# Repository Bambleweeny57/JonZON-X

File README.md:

# 🎵 JonZON-X AY-3-8910 Sound Expansion for ZX81

JonZON-X is a modern recreation of the ZON-X-81 Sound Box by Bi-Pak, designed for the ZX81. It uses the AY-3-8910 Programmable Sound Generator (PSG) and supports stereo line-out, optional multi-PSG expansion, and historically accurate address decoding.

This project prioritizes:
- ✅ Robust signal integrity
- ✅ Accurate control logic
- ✅ Modular expansion
- ✅ Historical preservation

---

## 🎯 Goals

- Recreate the original ZON-X-81 using AY-3-8910 (not AY-3-8912)
- Provide stereo line-out instead of onboard speaker
- Divide CPU clock as in the original design
- Support optional second and third PSGs via A5 and A6
- Document logic blocks and truth tables that match the actual schematic

---

## 🧠 Control Signal Logic

JonZON-X uses modern 74HC-series gates to derive control signals for the AY-3-8910. The address decoding is based on:

- **A0–A4**: Select the first PSG
- **A5**: Optional second PSG (replaces A4)
- **A6**: Optional third PSG (replaces A4)
- **A7**: Used in BC1 logic
- **/IOREQ**, **/WR**, **/RD**: Control timing

### Signal Derivation

| Signal | Logic Expression | Gates Used |
|--------|------------------|------------|
| **BDIR** | Derived from /IOREQ and /WR  
→ Routed through 74HC02 (inversion), 74HC08 (AND), and 74HC11 (3-input AND) | 74HC02, 74HC08, 74HC11 |
| **BC1** | Derived from /IOREQ, /WR, A2, A7, /RD  
→ Routed through 74HC02, 74HC08, and 74HC11 | 74HC02, 74HC08, 74HC11 |

There is **no AYSEL signal**—address selection is handled directly via A0–A4 (or A5/A6 for additional PSGs).

---

## 📊 Truth Table

| A0–A4 | A5/A6 | A2 | A7 | /IOREQ | /WR | /RD | BDIR | BC1 | Operation |
|------|-------|----|----|--------|-----|-----|------|-----|-----------|
| PSG 1 selected | —     | 1  | 1  | 0      | 0   | 1   | 1    | 1   | Write to register |
| PSG 1 selected | —     | 1  | 1  | 0      | 0   | 0   | 1    | 0   | Write to PSG |
| PSG 1 selected | —     | 1  | 1  | 0      | 1   | 0   | 0    | 1   | Read from PSG |
| PSG 2 selected | A5=1  | 1  | 1  | 0      | —   | —   | —    | —   | Optional second PSG |
| PSG 3 selected | A6=1  | 1  | 1  | 0      | —   | —   | —    | —   | Optional third PSG |
| Not selected   | —     | —  | —  | —      | —   | —   | 0    | 0   | Inactive |

---

## 🖼️ Visual Decode Logic

This schematic snippet shows how BDIR and BC1 are generated using 74HC02, 74HC08, and 74HC11 gates. Address selection is handled via A0–A4 (or A5/A6 for additional PSGs).

---

## 🎚️ DIP Switch Mapping for PSG Selection

JonZON-X supports up to three AY-3-8910 PSGs using configurable address lines via DIP switches. The DIP switches control A4, A5, and A6 to select which PSG is active.

| PSG   | A4 | A5 | A6 | Address (Binary) | Address (Decimal) |
|-------|----|----|----|------------------|-------------------|
| PSG1  | 1  | 0  | 0  | `11111111`       | 255               |
| PSG2  | 0  | 1  | 0  | `11101111`       | 239               |
| PSG3  | 0  | 0  | 1  | `11011111`       | 223               |

- **A4, A5, A6** are mutually exclusive: only one should be active at a time.
- These bits are part of the PSG register select address.
- DIP switches override the default A4–A6 lines from the ZX81.

This mapping allows users to select which PSG responds to register writes, enabling multi-chip expansion and stereo mixing.

---

## 📚 Historical References

- [ZON-X-81 Archive (1982 Bi-Pak)](https://archive.org/details/ZON_X-81_1982_Bi-Pak_GB)
- [RevSpace ZX81 PSG Expansion](https://revspace.nl/Zon_ZX-81_Programmable_Sound_Generator_expansion_for_ZX81PLUS35_with_working_SD-Card)
- [Mahjongg2 ZON-Compatible PSG](https://github.com/mahjongg2/ZON-compatible-PSG-with-SD-interface-for-ZX81plus35-ZX81)
- [Micromusic Article](https://www.muzines.co.uk/articles/micromusic/4456)
- [ZX8081 Clone Log](https://hackaday.io/project/184361-zx8081-homebrew-clone/log/203915-my-project-log-jan-mar2021)

---

## 🛠️ Future Plans

If the initial revision works, future additions may include:
- RAM and ROM expansion
- Joystick port
- Enhanced stereo mixing

---

### 🧪 Test 1: Test Routine

```basic
10 REM ZONTEST1
20 LET A=16514
30 POKE A,62
40 LET A=A+1
50 POKE A,0
60 LET A=A+1
70 POKE A,211
80 LET A=A+1
90 POKE A,0
100 LET A=A+1
110 POKE A,201
120 POKE 16515,7
130 POKE 16516,255
140 RAND USR 16514
150 POKE 16515,8
160 POKE 16516,191
170 RAND USR 16514
180 POKE 16515,13
190 POKE 16516,9
200 RAND USR 16514
210 GOTO 210
```
- 🔊 ZONTEST1 – Basic Tone Setup: [zontest1.p](https://github.com/jgratton72/JonZON-X/blob/master/Tests/zontest1.p)

### 🧪 Test 2: Envelope & Stereo Test

```basic
10 REM ZONTEST2
20 LET A=16514
30 POKE A,62
40 LET A=A+1
50 POKE A,0
60 LET A=A+1
70 POKE A,211
80 LET A=A+1
90 POKE A,0
100 LET A=A+1
110 POKE A,201
120 POKE 16515,7
130 POKE 16516,255
140 RAND USR 16514
150 POKE 16515,8
160 POKE 16516,191
170 RAND USR 16514
180 POKE 16515,13
190 POKE 16516,9
200 RAND USR 16514
210 LET E=0
220 POKE 16515,13
230 POKE 16516,E
240 RAND USR 16514
250 LET I=0
260 LET I=I+1
270 IF I<1000 THEN GOTO 260
280 LET E=E+1
290 IF E<16 THEN GOTO 220
300 GOTO 210
```
- 🎛️ ZONTEST2 – Envelope & Stereo: [zontest2.p](https://github.com/jgratton72/JonZON-X/blob/master/Tests/zontest2.p)

### 🧪 Test 3: Envelope Period Sweep

```basic
10 REM ZONTEST3
20 LET A=16514
30 POKE A,62
40 LET A=A+1
50 POKE A,0
60 LET A=A+1
70 POKE A,211
80 LET A=A+1
90 POKE A,0
100 LET A=A+1
110 POKE A,201
120 POKE 16515,7
130 POKE 16516,255
140 RAND USR 16514
150 POKE 16515,8
160 POKE 16516,191
170 RAND USR 16514
180 POKE 16515,13
190 POKE 16516,9
200 RAND USR 16514
210 LET P=0
220 POKE 16515,11
230 POKE 16516,P
240 RAND USR 16514
250 POKE 16515,12
260 POKE 16516,0
270 RAND USR 16514
280 LET I=0
290 LET I=I+1
300 IF I<1000 THEN GOTO 290
310 LET P=P+16
320 IF P<256 THEN GOTO 220
330 GOTO 210
```
- 📈 ZONTEST3 – Envelope Sweep: [zontest3.p](https://github.com/jgratton72/JonZON-X/blob/master/Tests/zontest3.p)

### 🧪 Test 4: DIP-Selectable PSG Verification

```basic
10 REM ZONTEST4
20 LET A=16514
30 POKE A,62
40 LET A=A+1
50 POKE A,0
60 LET A=A+1
70 POKE A,211
80 LET A=A+1
90 POKE A,0
100 LET A=A+1
110 POKE A,201
120 POKE 16515,8
130 POKE 16516,255
140 RAND USR 16514
150 LET I=0
160 LET I=I+1
170 IF I<500 THEN GOTO 160
180 POKE 16515,8
190 POKE 16516,239
200 RAND USR 16514
210 LET I=0
220 LET I=I+1
230 IF I<500 THEN GOTO 220
240 POKE 16515,8
250 POKE 16516,223
260 RAND USR 16514
270 LET I=0
280 LET I=I+1
290 IF I<500 THEN GOTO 280
300 GOTO 120
```
- 🎚️ ZONTEST4 – DIP-Selectable PSGs: [zontest4.p](https://github.com/jgratton72/JonZON-X/blob/master/Tests/zontest4.p)

---

## 📅 Revision History

### 🔧 Rev 1.0 Testing Note — Stereo Jack Adaptation
- **Socket Type:** 3-pin stereo jacks used in place of shunted 5-pin variants.
- **Pad Bridging:** Inner pads manually jumped to outer signal pads; ground positioned at center front.
- **Trade-off:** Left and Right channels will be reversed — acceptable for initial validation.
- **Rationale:** Simplifies early testing without requiring shunt headers. Prioritizes proof-of-function over stereo fidelity

### 🔄 Rev 1.1 — Audio Jack Correction
- **Issue:** Left and Right channels were misrouted via Shunts A and B.
- **Fix:** Channel A and B were reversed in the schematic to compensate for the physical swap.
- **Impact:** Stereo output now matches expected channel mapping. Updated KiCad files reflect this correction.

### 🔄 Rev 1.2 – Stereo Output Mapping Adjustment

- **Issue**: Legacy ZON-X-81 software frequently routes noise to Channel B, but JonZON-X previously mixed Channel C to both outputs (a common pattern in other PSG devices, including the ZX Spectrum 128K). This caused noise effects to be isolated to the right channel or lost in stereo playback.
- **Fix**: Remapped stereo output:
  - Channel A → Left
  - Channel B → Mixed (Left + Right)
  - Channel C → Right  
  This ensures Channel B (the legacy noise channel) is centered in stereo output.
- **Impact**: Improved compatibility with original ZON-X-81 programs and demos. Noise effects now play as intended across both channels, preserving the sonic balance of legacy software.

### 🔄 Rev 1.3 – Logic Footprint Correction
- **Issue**: 74HTC Logic IC footprints where set as 400mil wide not 300mil.
- **Fix**: Change footprints:
  - Corrected 74HCT logic IC footprints from 400mil to 300mil for proper socket fit.
  - Updated KiCad symbols and PCB layout to reflect accurate DIP sizing.
- **Impact**: Improves build reliability and simplifies future revisions.

### 🔄 Rev 1.4 – Dual PSG Support & Expansion-Ready Logic

- 🧩 **Added AY-3-8912 schematic symbol** to Rev 1.3 base, enabling direct support for legacy demos and stereo output
- 🧠 **Dual PSG compatibility**: Supports both AY-3-8910 and AY-3-8912 via shared footprint and modular decoding logic
- 🧰 **Decoding logic updated** to include `/RD` line—reserved for future expansion (e.g. SD card interfacing via Port A)
- 🛠️ **Maintains Rev 1.3 write logic** for AY-3-8910 while enabling seamless upgrade path to AY-3-8912
- 🎶 **Verified compatibility** with original ULA and both HCT and F-series logic—multi scroll and Viaduct demos pass cleanly with AY-3-8912
- ⚠️ **VLA81 compatibility issues noted**: Viaduct demo fails to run reliably due to timing sensitivity and address decoding quirks. Detaching A15 improves behavior in some cases but does not fully resolve playback issues. Original ULA remains the recommended option for stable demo performance.
- 📘 **README and onboarding overlays updated** to reflect dual-chip support and future expansion notes

> Rev 1.4 preserves the modular ethos of JonZON-X while enabling legacy fidelity and future-proofed decoding. Component back-mounting and through-hole edge connector support are planned for a future revision.

---

## 🧩 Rev1.x Closure Summary

The Rev1.x series of JONZON-X-81 boards concludes with **Rev1.4**, marking the final iteration of this foundational phase. Throughout development, multiple configurations were explored to optimize PSG register selection and compatibility:

- **AY-3-8910** with grounded Port B showed partial success in register selection, but inconsistencies remained—especially when paired with **74F logic**.
- Transitioning to **AY-3-8912** and **74HCT logic** yielded flawless register selection across demo routines, confirming a stable configuration.

Based on these findings, Rev1.4 is the final release in the Rev1.x lineage. All future development will pivot to **Rev2.0**, which will:

- Standardize on the **AY-3-8912** sound chip.
- Feature **back-mounted components** for cleaner top-side access.
- Introduce a **through-hole edge connector** to support future expansions.
- Include a **development header** exposing A0–A7, 5V, and GND—enabling both sound card interfacing and SD card experimentation via Port A.

Documentation for Rev1.x will remain available for reference and legacy compatibility. Contributors are encouraged to migrate to the Rev2.0 repo for ongoing development and community collaboration.

---

## 📝 Notes

This is my first KiCad project and GitHub repo. While I’ve used other EDA tools and GitHub before, this is a learning curve and a preservation effort.

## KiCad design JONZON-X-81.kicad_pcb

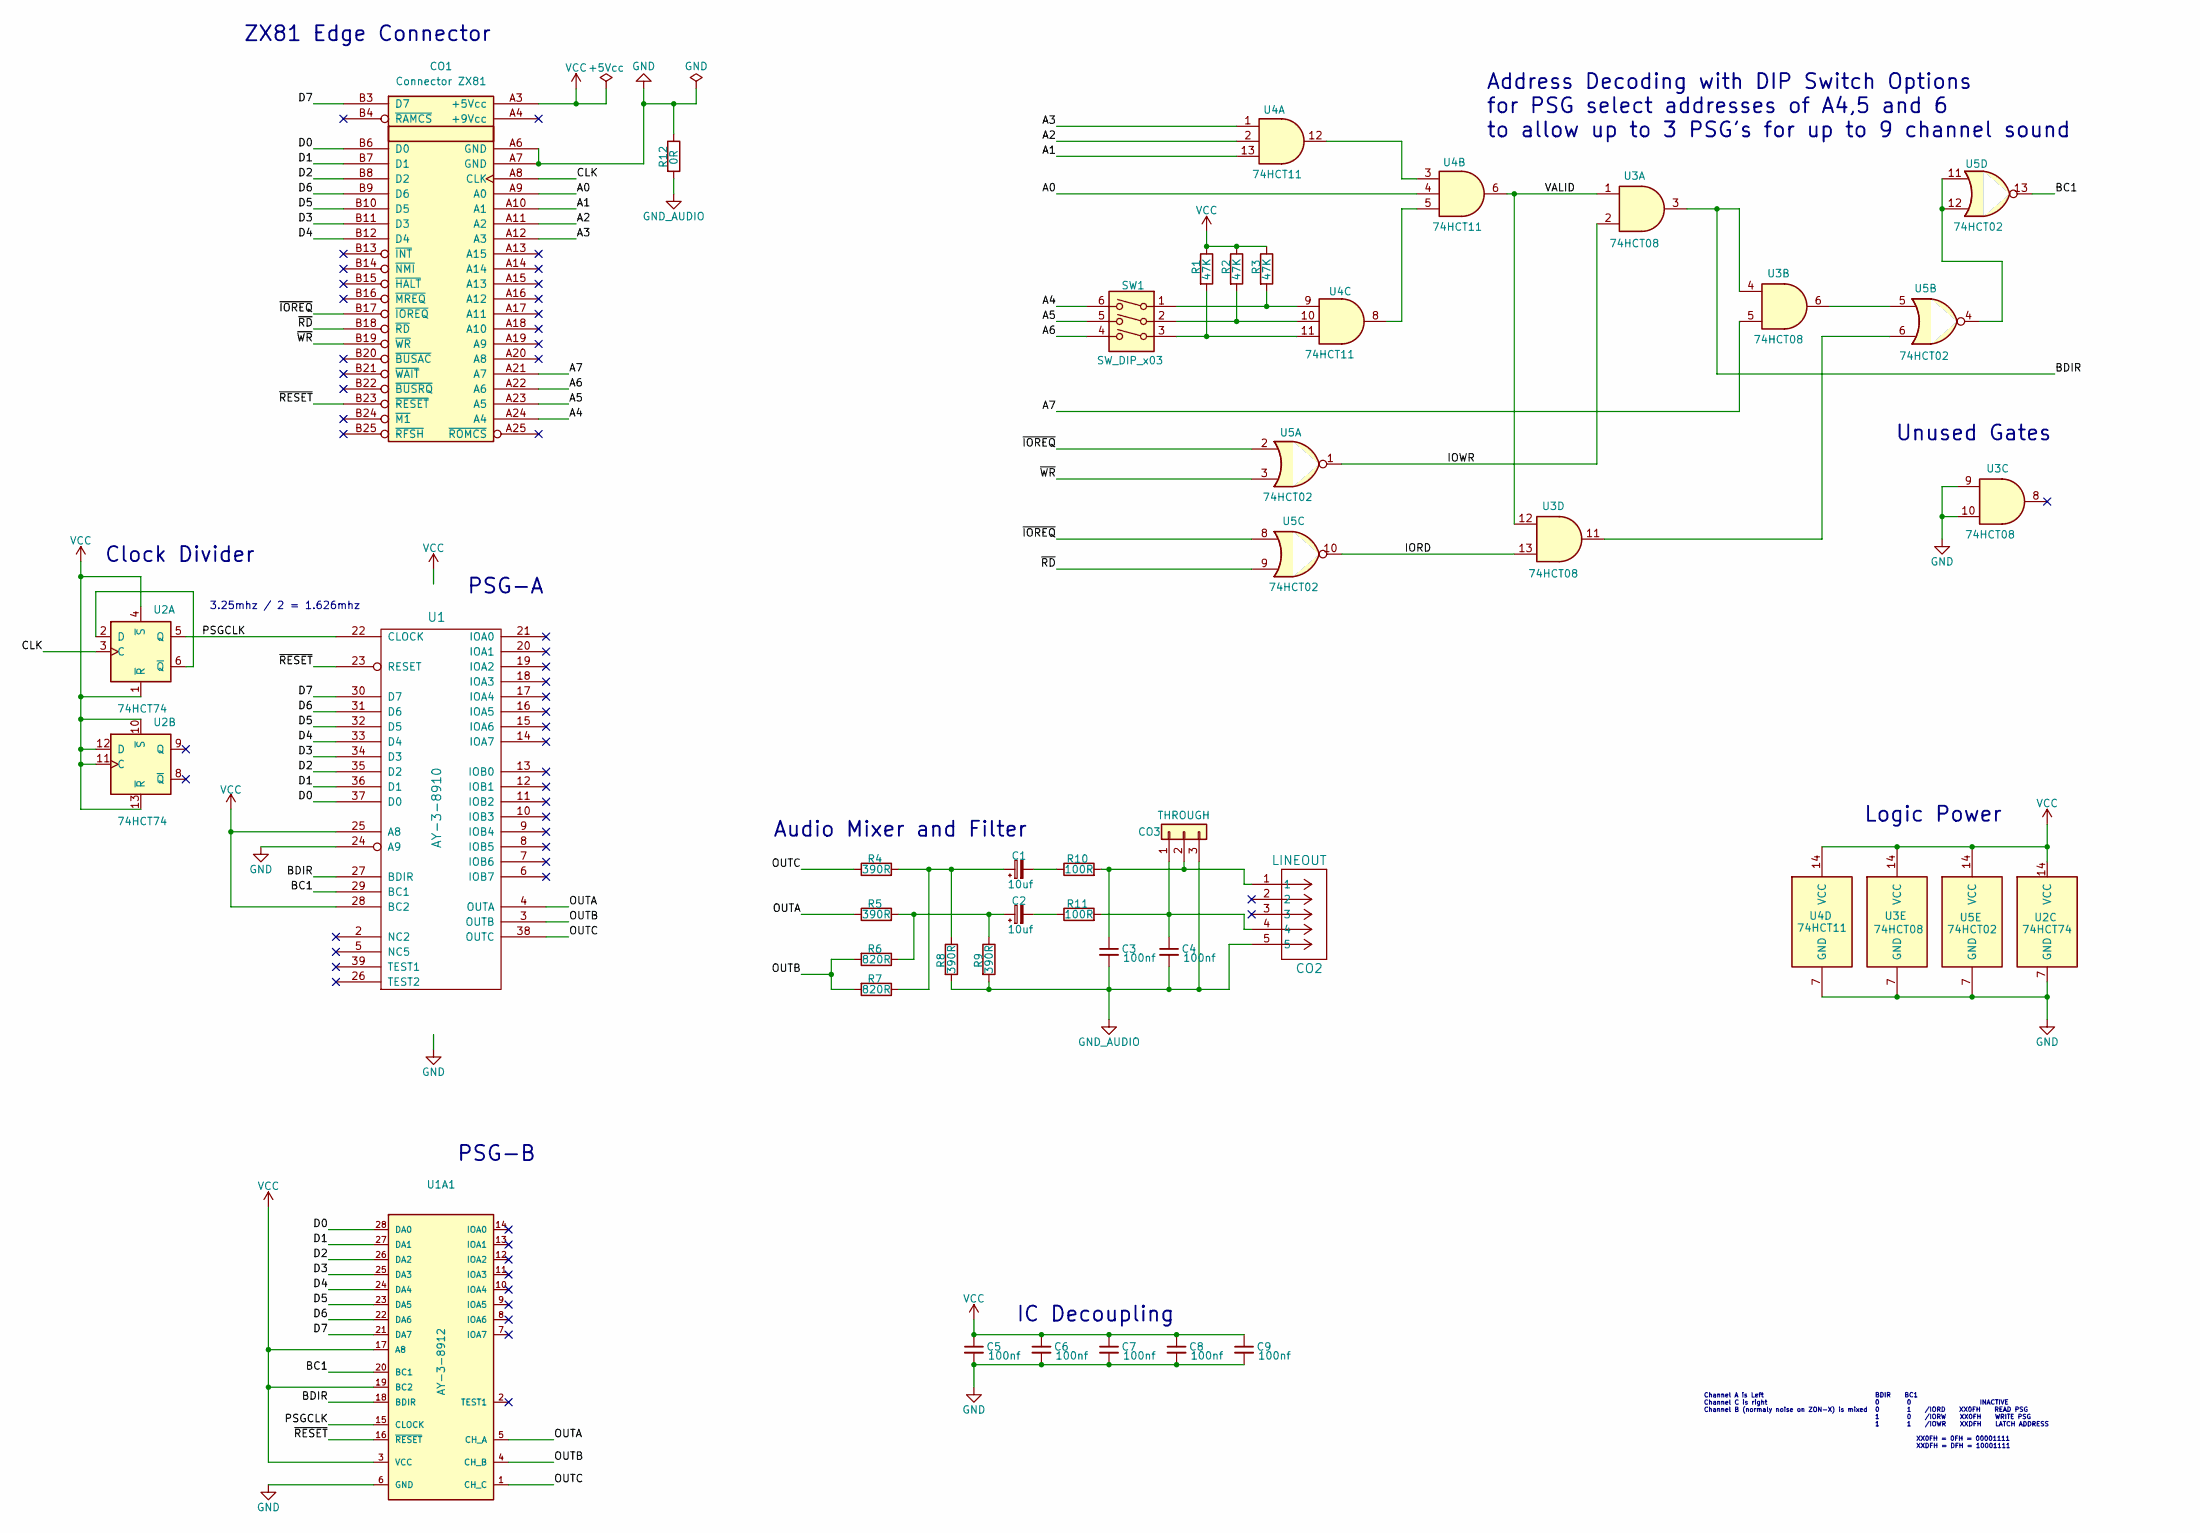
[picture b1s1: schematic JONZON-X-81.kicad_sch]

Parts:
C1, C2: 10uf; CP_Radial_D5.0mm_P2.00mm
C3, C4, C5, C6, C7, C8, C9: 100nf; C_Disc_D3.0mm_W1.6mm_P2.50mm
CO1: Connector ZX81; EDGE ZX81 TOP
CO2: LINEOUT; CONN5_SPC21348_MTC
CO3: THROUGH; PinHeader_1x03_P2.54mm_Vertical
R1, R2, R3: 47K; R_Axial_DIN0207_L6.3mm_D2.5mm_P7.62mm_Horizontal
R4, R5, R8, R9: 390R; R_Axial_DIN0207_L6.3mm_D2.5mm_P7.62mm_Horizontal
R6, R7: 820R; R_Axial_DIN0207_L6.3mm_D2.5mm_P7.62mm_Horizontal
R10, R11: 100R; R_Axial_DIN0207_L6.3mm_D2.5mm_P7.62mm_Horizontal
R12: 0R; R_Axial_DIN0207_L6.3mm_D2.5mm_P7.62mm_Horizontal
SW1: SW_DIP_x03; SW_DIP_SPSTx03_Slide_9.78x9.8mm_W7.62mm_P2.54mm
U1: AY-3-8910; DIP-40_W15.24mm_LongPads
U1A1: AY-3-8912; DIP-28_W15.24mm_LongPads
U2: 74HCT74; DIP-14_W7.62mm_Socket_LongPads
U3: 74HCT08; DIP-14_W7.62mm_Socket_LongPads
U4: 74HCT11; DIP-14_W7.62mm_Socket_LongPads
U5: 74HCT02; DIP-14_W7.62mm_Socket_LongPads

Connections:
/A0: CO1.A9 (A0), U4.4
/A1: CO1.A10 (A1), U4.13
/A2: CO1.A11 (A2), U4.2
/A3: CO1.A12 (A3), U4.1
/A4: CO1.A24 (A4), SW1.6
/A5: CO1.A23 (A5), SW1.5
/A6: CO1.A22 (A6), SW1.4
/A7: CO1.A21 (A7), U3.5
/BC1: U1.29 (BC1), U1A1.20 (BC1), U5.13; also elsewhere on the board
/BDIR: U1.27 (BDIR), U1A1.18 (BDIR), U3.3, U3.4; also elsewhere on the board
/CLK: CO1.A8 (CLK), U2.3 (C)
/D0: CO1.B6 (D0), U1.37 (D0), U1A1.28 (DA0); also elsewhere on the board
/D1: CO1.B7 (D1), U1.36 (D1), U1A1.27 (DA1); also elsewhere on the board
/D2: CO1.B8 (D2), U1.35 (D2), U1A1.26 (DA2); also elsewhere on the board
/D3: CO1.B11 (D3), U1.34 (D3), U1A1.25 (DA3); also elsewhere on the board
/D4: CO1.B12 (D4), U1.33 (D4), U1A1.24 (DA4); also elsewhere on the board
/D5: CO1.B10 (D5), U1.32 (D5), U1A1.23 (DA5); also elsewhere on the board
/D6: CO1.B9 (D6), U1.31 (D6), U1A1.22 (DA6); also elsewhere on the board
/D7: CO1.B3 (D7), U1.30 (D7), U1A1.21 (DA7); also elsewhere on the board
/IORD: U3.13, U5.10
/IOWR: U3.2, U5.1
/OUTA: R5.1, U1.4 (OUTA), U1A1.5 (CH_A); also elsewhere on the board
/OUTB: R6.2, R7.2, U1.3 (OUTB), U1A1.4 (CH_B); also elsewhere on the board
/OUTC: R4.1, U1.38 (OUTC), U1A1.1 (CH_C); also elsewhere on the board
/PSGCLK: U1.22 (CLOCK), U1A1.15 (CLOCK), U2.5 (Q); also elsewhere on the board
/VALID: U3.1, U3.12, U4.6
/~IOREQ: CO1.B17 (~IOREQ), U5.2, U5.8
/~RD: CO1.B18 (~RD), U5.9
/~RESET: CO1.B23 (~RESET), U1.23 (RESET), U1A1.16 (~RESET); also elsewhere on the board
/~WR: CO1.B19 (~WR), U5.3
GND: C5.2, C6.2, C7.2, C8.2, C9.2, CO1.A6 (GND), CO1.A7 (GND), R12.1, U1.1 (GND), U1.24 (A9), U1A1.6 (GND), U2.7 (GND), U3.7 (GND), U3.9, U3.10, U4.7 (GND), U5.7 (GND); also elsewhere on the board
GND_AUDIO: C3.2, C4.2, CO2.5, CO3.3, R8.2, R9.2, R12.2; also elsewhere on the board
unnamed: C1.1, R4.2, R7.1, R8.1
unnamed: C1.2, R10.1
unnamed: C2.1, R5.2, R6.1, R9.1
unnamed: C2.2, R11.1
unnamed: C4.1, CO2.4, CO3.1, R11.2
unnamed: C3.1, CO2.1, CO3.2, R10.2
unnamed: R1.2, SW1.3, U4.11
unnamed: R2.2, SW1.2, U4.10
unnamed: R3.2, SW1.1, U4.9
unnamed: U2.2 (D), U2.6 (~Q)
unnamed: U3.6, U5.5
unnamed: U3.11, U5.6
unnamed: U4.5, U4.8
unnamed: U4.3, U4.12
unnamed: U5.4, U5.11, U5.12
VCC: C5.1, C6.1, C7.1, C8.1, C9.1, CO1.A3 (+5Vcc), R1.1, R2.1, R3.1, U1.25 (A8), U1.28 (BC2), U1.40 (VCC), U1A1.3 (VCC), U1A1.17 (A8), U1A1.19 (BC2), U2.1 (~R), U2.4 (~S), U2.10 (~S), U2.11 (C), U2.12 (D), U2.13 (~R), U2.14 (VCC), U3.14 (VCC), U4.14 (VCC), U5.14 (VCC); also elsewhere on the board

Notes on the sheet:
Address Decoding with DIP Switch Options for PSG select addresses of A4,5 and 6 to allow up to 3 PSG's for up to 9 channel sound
ZX81 Edge Connector
PSG-A
IC Decoupling
Clock Divider
Logic Power
PSG-B
Unused Gates
BDIR BC1 0 0 INACTIVE 0 1 /IORD XX0FH READ PSG 1 0 /IORW XX0FH WRITE PSG 1 1 /IOWR XXDFH LATCH ADDRESS XX0FH = 0FH = 00001111 XXDFH = DFH = 10001111
Channel A is Left Channel C is right Channel B (normaly noise on ZON-X) is mixed
Audio Mixer and Filter
3.25mhz / 2 = 1.626mhz

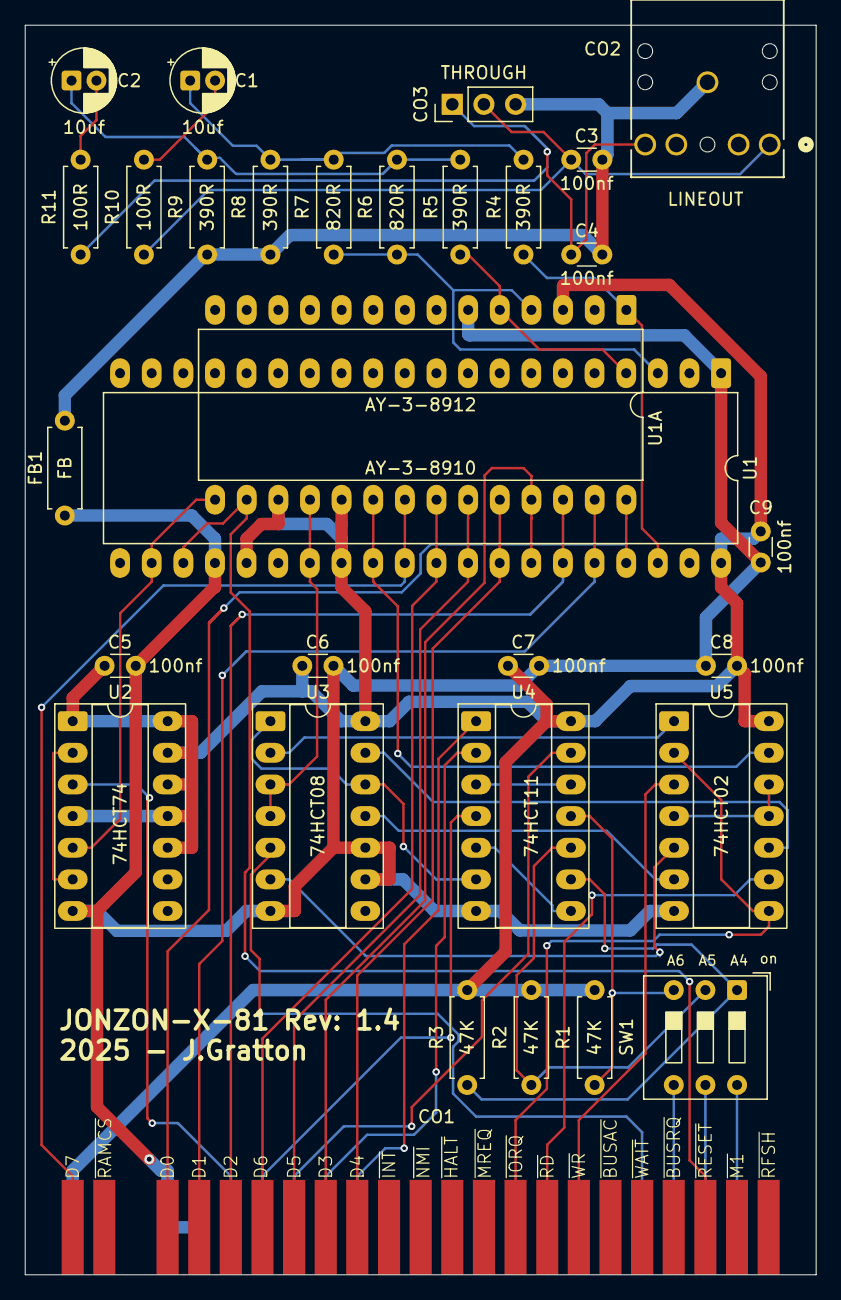
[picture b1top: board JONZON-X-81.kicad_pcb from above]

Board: 2 copper layers, 63.5 x 100.3 mm, 31 parts (0 on the bottom side), 48 nets.

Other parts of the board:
FB1: FB; R_Axial_DIN0207_L6.3mm_D2.5mm_P7.62mm_Horizontal
U1A: AY-3-8912; DIP-28_W15.24mm_LongPads

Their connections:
/BC1: U1A.20 (BC1); also elsewhere on the board
/BDIR: U1A.18 (BDIR); also elsewhere on the board
/D0: U1A.28 (DA0); also elsewhere on the board
/D1: U1A.27 (DA1); also elsewhere on the board
/D2: U1A.26 (DA2); also elsewhere on the board
/D3: U1A.25 (DA3); also elsewhere on the board
/D4: U1A.24 (DA4); also elsewhere on the board
/D5: U1A.23 (DA5); also elsewhere on the board
/D6: U1A.22 (DA6); also elsewhere on the board
/D7: U1A.21 (DA7); also elsewhere on the board
/OUTA: U1A.5 (CH_A); also elsewhere on the board
/OUTB: U1A.4 (CH_B); also elsewhere on the board
/OUTC: U1A.1 (CH_C); also elsewhere on the board
/PSGCLK: U1A.15 (CLOCK); also elsewhere on the board
/~RESET: U1A.16 (~RESET); also elsewhere on the board
GND: FB1.1, U1A.6 (GND); also elsewhere on the board
GND_AUDIO: FB1.2; also elsewhere on the board
VCC: U1A.3 (VCC), U1A.17 (A8), U1A.19 (BC2); also elsewhere on the board

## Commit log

2025-08-01 change 1
2025-08-01 commit 2
2025-08-01 commit 3
2025-08-01 commit 4
2025-08-01 added clock
2025-08-02 Added new ZX81 Edge Connector and Decoupling
2025-08-03 local changes
2025-08-03 Added podt coupling output filtering
2025-08-03 realigened autio out stage
2025-08-04 A7 was missaligned Added text to show detail of channel mixing on audio
2025-08-05 Added Audio interconnect Added extra nots for Addressing
2025-08-06 Added VCC and GND Added Power Suuply to IC's Commented 3 ERC warnings re bidirectional pins for 5v and GND for the ZX81 Connector
2025-08-06 remove erc report.
2025-08-06 Channged Channel A and B over on the audio mixer as they would have been the wrong way to what I intended.
2025-08-06 updated schematic pdf
2025-08-08 added just two power inputs for +5Vcc to VCC and GND to GND Created commented ERC warning as +5Vcc and GND are bidirectional by design. Move a few of the text comments to make the schematic look neat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
2025-08-08 Started PCB
2025-08-08 Added Auto Jack Added Board outline Layed out some components in Board outline
2025-08-08 Added 3D view Image
2025-08-11 Routed PCB first pass Updated footprint for Audio Line Out Jack Added 3D model for Audio Line Out Jack Updated Schematic PDF Updated 3D Image
2025-08-11 Added iBOM
2025-08-11 Added Fab Files Added Revision to PCB
2025-08-11 Tidy up
2025-08-12 Changed Label on LINEIN to THROUGH Added seperate Ground and Audio Ground Added 0ohm link for Ground to Audio Ground link Could be a Ferrite Bead
2025-08-12 Updatred Read me again
2025-08-12 Update Readme again
2025-08-12 upade 3D model of PCB
2025-08-12 Update Design Check on PCB
2025-08-12 Renamed files Added Ground and Audio Ground Planes Moved Ground Bridge to be between ground planes Generated some new images
2025-08-12 Changed PDF Name Chnage Decoupling area to IC Decupling
2025-08-12 New fab files
2025-08-12 Updated iBOM
2025-08-12 rename
2025-08-15 Pulled /A9 low
2025-08-15 updated readme.
2025-08-15 updated lots of things
2025-08-16 fenced and stiched ground planes
2025-08-16 removed fab files
2025-08-16 built new fab files
2025-08-16 corrected connections on audio jack as the footprint does not match the schematic symbol pinout. the left and right where on rev 1.0 connected to shunts a and b. to correct this I will just place sho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
2025-08-16 upated readme
2025-08-16 commented rev 1.1 on the PCB
2025-08-16 updated rev 1.1 and readme.
2025-08-16 added better formating for the revision history.
2025-08-16 added testing note for rev 1.0 to readme.
2025-08-16 update rev history
2025-08-25 added rev 1.3 to revision history.
2025-08-25 updated tests to poke machine code.
2025-08-25 added .p versions of the test programs 1-4.
2025-08-25 added urls to the tests in the readme to download the .p file for each.
2025-08-25 added image for psg selection logic
2025-08-25 added image of psg selection logic to readme
2025-08-25 created new rev 1.3 fab files. updated gerber view images to rev 1.3. removed older revision fab files.
2025-08-25 change routing on d6
2025-08-25 updated left channel route.
2025-09-05 Archiving Project at v1.3 Starting a fresh as a v2.0 with simplified logic.
2025-09-05 updated readerme to reflect the change of direction in v2.0
2025-09-05 V2.0 start
2025-09-06 built rev2.0 schematic pdf
2025-09-11 rev 1.3
2025-09-11 removed backups
2025-09-13 rev 1.4 start adding AY-3-8912
2025-09-13 Added AY-3-8912 as an optional PSG to the Schematic. Created new v1.4 PDF.
2025-09-13 Created rev 1.4 Fab File and Images
